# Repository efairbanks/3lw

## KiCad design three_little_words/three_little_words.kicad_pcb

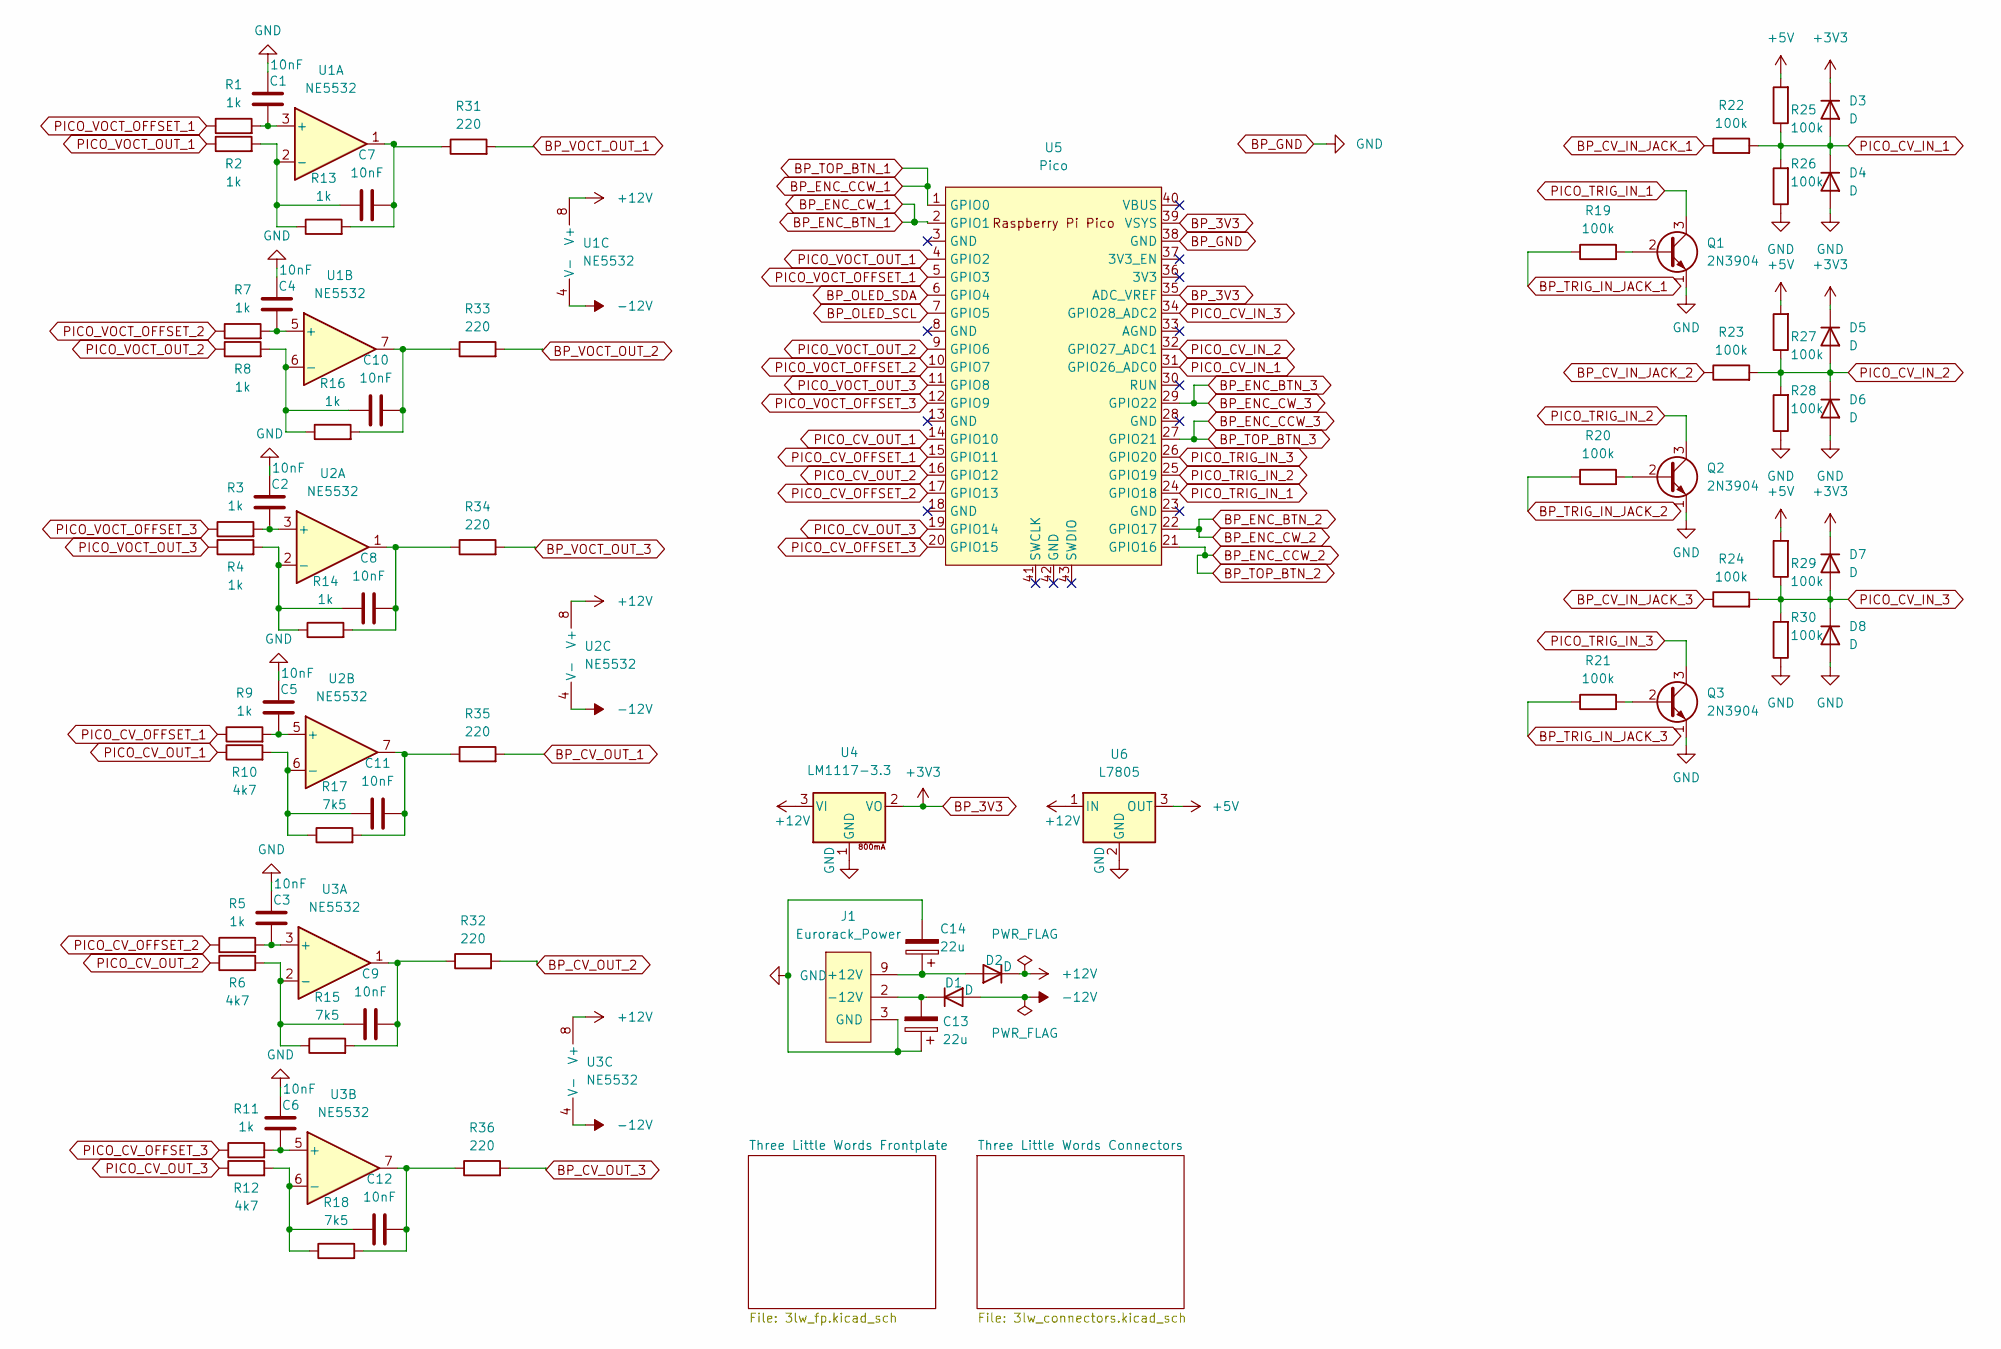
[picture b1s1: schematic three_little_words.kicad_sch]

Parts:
C1, C2, C3, C4, C5, C6, C7, C8, C9, C10, C11, C12: 10nF; C_Disc_D8.0mm_W2.5mm_P5.00mm
C13, C14: 22u; CP_Radial_D5.0mm_P2.50mm
D1, D2: D; D_DO-41_SOD81_P7.62mm_Horizontal
D3, D4, D5, D6, D7, D8: D; D_DO-35_SOD27_P7.62mm_Horizontal
J1: Eurorack_Power; mpn 302-S101
Q1, Q2, Q3: 2N3904; TO-92_Inline
R1, R2, R3, R4, R5, R7, R8, R9, R11, R13, R14, R16: 1k; R_Axial_DIN0207_L6.3mm_D2.5mm_P7.62mm_Horizontal
R6, R10, R12: 4k7; R_Axial_DIN0207_L6.3mm_D2.5mm_P7.62mm_Horizontal
R15, R17, R18: 7k5; R_Axial_DIN0207_L6.3mm_D2.5mm_P7.62mm_Horizontal
R19, R20, R21, R22, R23, R24, R25, R26, R27, R28, R29, R30: 100k; R_Axial_DIN0207_L6.3mm_D2.5mm_P7.62mm_Horizontal
R31, R32, R33, R34, R35, R36: 220; R_Axial_DIN0207_L6.3mm_D2.5mm_P7.62mm_Horizontal
U1, U2, U3: NE5532; DIP-8_W7.62mm
U4: LM1117-3.3; TO-220-3_Vertical; mpn LM1117IMP-3.3
U5: Pico; RPi_Pico_SMD_TH
U6: L7805; TO-220-3_Vertical

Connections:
+5V: R25.2, R27.2, R29.2, U6.3 (OUT)
+12V: D2.1 (K), U1.8 (V+), U2.8 (V+), U3.8 (V+), U4.3 (VI), U6.1 (IN)
-12V: D1.2 (A), U1.4 (V-), U2.4 (V-), U3.4 (V-)
BP_3V3: D3.1 (K), D5.1 (K), D7.1 (K), U4.2 (VO), U5.35 (ADC_VREF), U5.39 (VSYS); also elsewhere on the board
BP_CV_IN_JACK_1: R22.1; also elsewhere on the board
BP_CV_IN_JACK_2: R23.1; also elsewhere on the board
BP_CV_IN_JACK_3: R24.1; also elsewhere on the board
BP_CV_OUT_1: R35.2; also elsewhere on the board
BP_CV_OUT_2: R32.2; also elsewhere on the board
BP_CV_OUT_3: R36.2; also elsewhere on the board
BP_ENC_BTN_1: U5.2 (GPIO1); also elsewhere on the board
BP_ENC_BTN_2: U5.22 (GPIO17); also elsewhere on the board
BP_ENC_BTN_3: U5.29 (GPIO22); also elsewhere on the board
BP_ENC_CCW_1: U5.1 (GPIO0); also elsewhere on the board
BP_ENC_CCW_2: U5.21 (GPIO16); also elsewhere on the board
BP_ENC_CCW_3: U5.27 (GPIO21); also elsewhere on the board
BP_GND: C1.1, C2.1, C3.1, C4.1, C5.1, C6.1, C13.1, C14.2, D4.2 (A), D6.2 (A), D8.2 (A), J1.3 (GND), J1.4 (GND), J1.5 (GND), J1.6 (GND), J1.7 (GND), J1.8 (GND), Q1.1 (E), Q2.1 (E), Q3.1 (E), R26.1, R28.1, R30.1, U4.1 (GND), U5.38 (GND), U6.2 (GND); also elsewhere on the board
BP_OLED_SCL: U5.7 (GPIO5); also elsewhere on the board
BP_OLED_SDA: U5.6 (GPIO4); also elsewhere on the board
BP_TRIG_IN_JACK_1: R19.1; also elsewhere on the board
BP_TRIG_IN_JACK_2: R20.1; also elsewhere on the board
BP_TRIG_IN_JACK_3: R21.1; also elsewhere on the board
BP_VOCT_OUT_1: R31.2; also elsewhere on the board
BP_VOCT_OUT_2: R33.2; also elsewhere on the board
BP_VOCT_OUT_3: R34.2; also elsewhere on the board
unnamed: C1.2, R1.2, U1.3 (+)
unnamed: C2.2, R3.2, U2.3 (+)
unnamed: C3.2, R5.2, U3.3 (+)
unnamed: C4.2, R7.2, U1.5 (+)
unnamed: C5.2, R9.2, U2.5 (+)
unnamed: C6.2, R11.2, U3.5 (+)
unnamed: C7.1, R2.2, R13.1, U1.2 (-)
unnamed: C7.2, R13.2, R31.1, U1.1
unnamed: C8.1, R4.2, R14.1, U2.2 (-)
unnamed: C8.2, R14.2, R34.1, U2.1
unnamed: C9.1, R6.2, R15.1, U3.2 (-)
unnamed: C9.2, R15.2, R32.1, U3.1
unnamed: C10.1, R8.2, R16.1, U1.6 (-)
unnamed: C10.2, R16.2, R33.1, U1.7
unnamed: C11.1, R10.2, R17.1, U2.6 (-)
unnamed: C11.2, R17.2, R35.1, U2.7
unnamed: C12.1, R12.2, R18.1, U3.6 (-)
unnamed: C12.2, R18.2, R36.1, U3.7
unnamed: C13.2, D1.1 (K), J1.1 (-12V), J1.2 (-12V)
unnamed: C14.1, D2.2 (A), J1.9 (+12V), J1.10 (+12V)
unnamed: Q1.2 (B), R19.2
unnamed: Q2.2 (B), R20.2
unnamed: Q3.2 (B), R21.2
PICO_CV_IN_1: D3.2 (A), D4.1 (K), R22.2, R25.1, R26.2, U5.31 (GPIO26_ADC0)
PICO_CV_IN_2: D5.2 (A), D6.1 (K), R23.2, R27.1, R28.2, U5.32 (GPIO27_ADC1)
PICO_CV_IN_3: D7.2 (A), D8.1 (K), R24.2, R29.1, R30.2, U5.34 (GPIO28_ADC2)
PICO_CV_OFFSET_1: R9.1, U5.15 (GPIO11)
PICO_CV_OFFSET_2: R5.1, U5.17 (GPIO13)
PICO_CV_OFFSET_3: R11.1, U5.20 (GPIO15)
PICO_CV_OUT_1: R10.1, U5.14 (GPIO10)
PICO_CV_OUT_2: R6.1, U5.16 (GPIO12)
PICO_CV_OUT_3: R12.1, U5.19 (GPIO14)
PICO_TRIG_IN_1: Q1.3 (C), U5.24 (GPIO18)
PICO_TRIG_IN_2: Q2.3 (C), U5.25 (GPIO19)
PICO_TRIG_IN_3: Q3.3 (C), U5.26 (GPIO20)
PICO_VOCT_OFFSET_1: R1.1, U5.5 (GPIO3)
PICO_VOCT_OFFSET_2: R7.1, U5.10 (GPIO7)
PICO_VOCT_OFFSET_3: R3.1, U5.12 (GPIO9)
PICO_VOCT_OUT_1: R2.1, U5.4 (GPIO2)
PICO_VOCT_OUT_2: R8.1, U5.9 (GPIO6)
PICO_VOCT_OUT_3: R4.1, U5.11 (GPIO8)

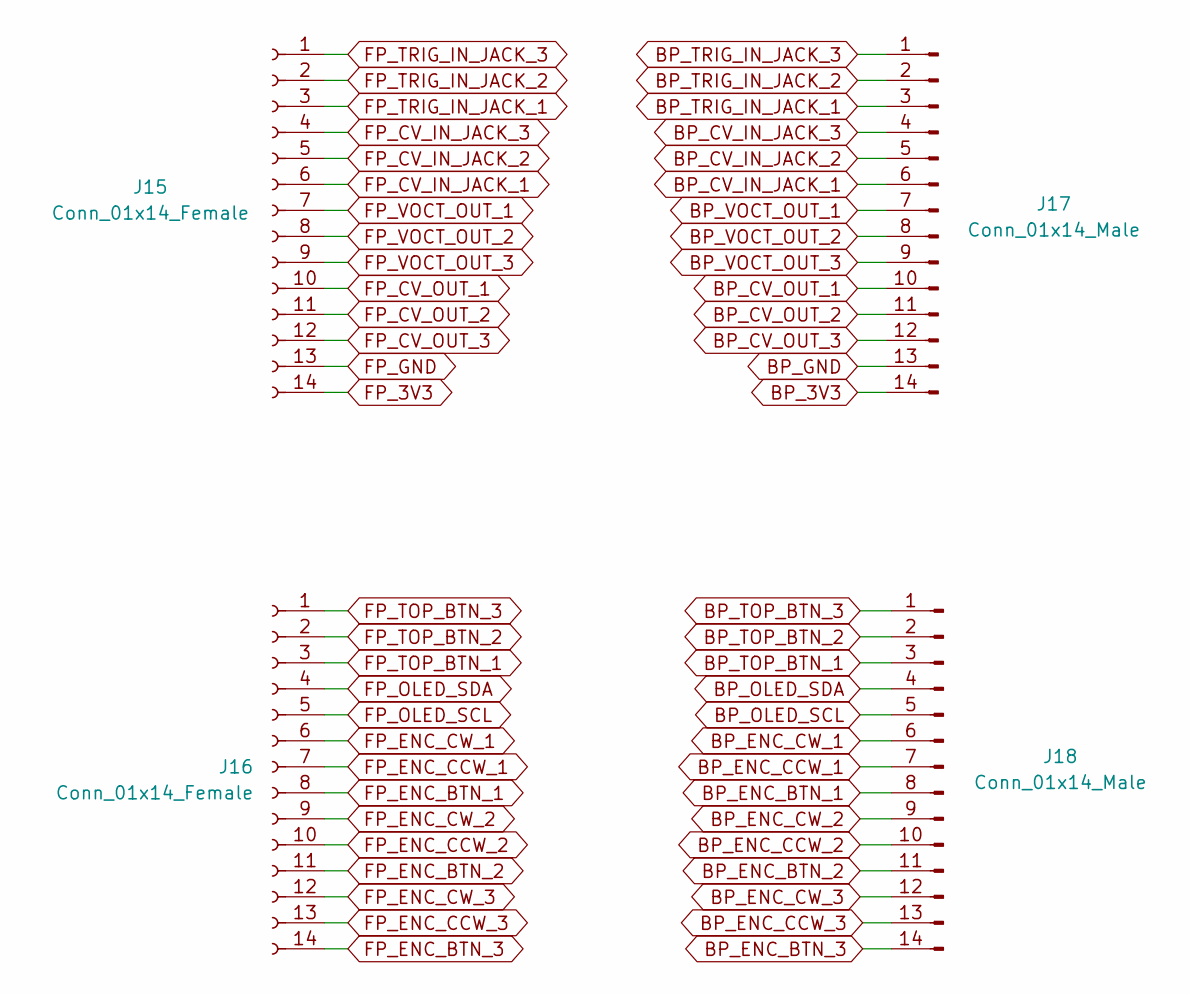
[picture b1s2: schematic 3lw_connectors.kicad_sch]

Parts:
J15, J16: Conn_01x14_Female; PinSocket_1x14_P2.54mm_Vertical
J17, J18: Conn_01x14_Male; PinHeader_1x14_P2.54mm_Vertical

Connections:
BP_3V3: J17.14; also elsewhere on the board
BP_CV_IN_JACK_1: J17.6; also elsewhere on the board
BP_CV_IN_JACK_2: J17.5; also elsewhere on the board
BP_CV_IN_JACK_3: J17.4; also elsewhere on the board
BP_CV_OUT_1: J17.10; also elsewhere on the board
BP_CV_OUT_2: J17.11; also elsewhere on the board
BP_CV_OUT_3: J17.12; also elsewhere on the board
BP_ENC_BTN_1: J18.6, J18.8; also elsewhere on the board
BP_ENC_BTN_2: J18.9, J18.11; also elsewhere on the board
BP_ENC_BTN_3: J18.12, J18.14; also elsewhere on the board
BP_ENC_CCW_1: J18.3, J18.7; also elsewhere on the board
BP_ENC_CCW_2: J18.2, J18.10; also elsewhere on the board
BP_ENC_CCW_3: J18.1, J18.13; also elsewhere on the board
BP_GND: J17.13; also elsewhere on the board
BP_OLED_SCL: J18.5; also elsewhere on the board
BP_OLED_SDA: J18.4; also elsewhere on the board
BP_TRIG_IN_JACK_1: J17.3; also elsewhere on the board
BP_TRIG_IN_JACK_2: J17.2; also elsewhere on the board
BP_TRIG_IN_JACK_3: J17.1; also elsewhere on the board
BP_VOCT_OUT_1: J17.7; also elsewhere on the board
BP_VOCT_OUT_2: J17.8; also elsewhere on the board
BP_VOCT_OUT_3: J17.9; also elsewhere on the board
FP_3V3: J15.14; also elsewhere on the board
FP_CV_IN_JACK_1: J15.6; also elsewhere on the board
FP_CV_IN_JACK_2: J15.5; also elsewhere on the board
FP_CV_IN_JACK_3: J15.4; also elsewhere on the board
FP_CV_OUT_1: J15.10; also elsewhere on the board
FP_CV_OUT_2: J15.11; also elsewhere on the board
FP_CV_OUT_3: J15.12; also elsewhere on the board
FP_ENC_BTN_1: J16.8; also elsewhere on the board
FP_ENC_BTN_2: J16.11; also elsewhere on the board
FP_ENC_BTN_3: J16.14; also elsewhere on the board
FP_ENC_CCW_1: J16.7; also elsewhere on the board
FP_ENC_CCW_2: J16.10; also elsewhere on the board
FP_ENC_CCW_3: J16.13; also elsewhere on the board
FP_ENC_CW_1: J16.6; also elsewhere on the board
FP_ENC_CW_2: J16.9; also elsewhere on the board
FP_ENC_CW_3: J16.12; also elsewhere on the board
FP_OLED_SCL: J16.5; also elsewhere on the board
FP_OLED_SDA: J16.4; also elsewhere on the board
FP_TOP_BTN_1: J16.3; also elsewhere on the board
FP_TOP_BTN_2: J16.2; also elsewhere on the board
FP_TOP_BTN_3: J16.1; also elsewhere on the board
FP_TRIG_IN_JACK_1: J15.3; also elsewhere on the board
FP_TRIG_IN_JACK_2: J15.2; also elsewhere on the board
FP_TRIG_IN_JACK_3: J15.1; also elsewhere on the board
FP_VOCT_OUT_1: J15.7; also elsewhere on the board
FP_VOCT_OUT_2: J15.8; also elsewhere on the board
FP_VOCT_OUT_3: J15.9; also elsewhere on the board

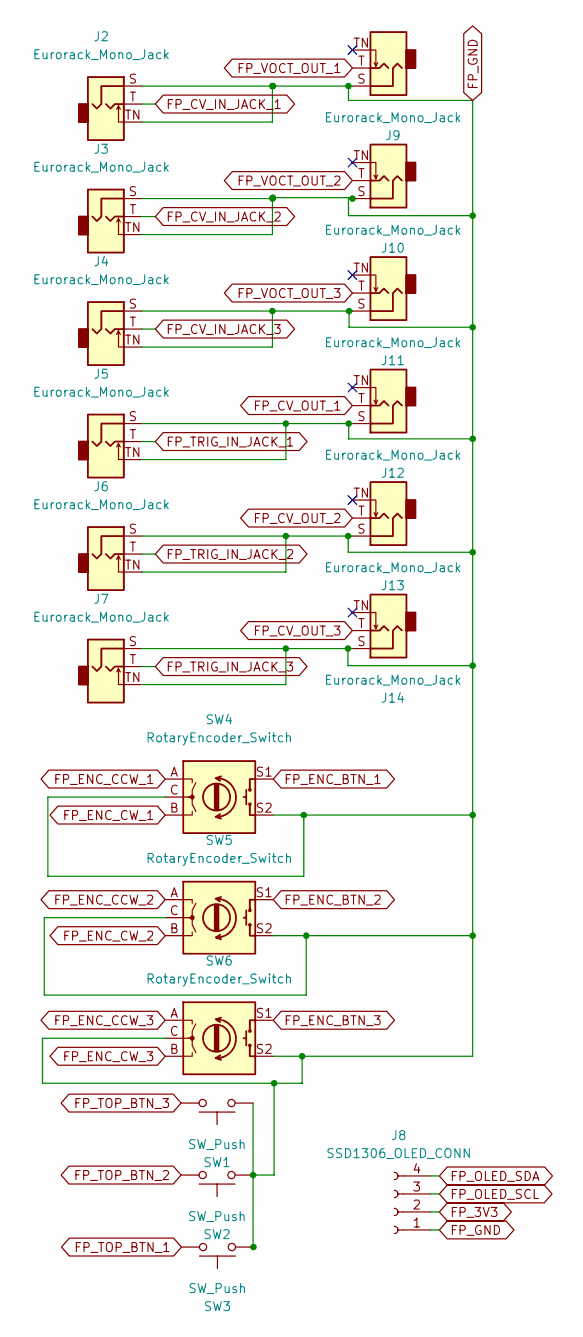
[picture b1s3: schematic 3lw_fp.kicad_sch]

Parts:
J2, J3, J4, J5, J6, J7, J9, J10, J11, J12, J13, J14: Eurorack_Mono_Jack; WQP518MA; mpn WQP-WQP518MA
J8: SSD1306_OLED_CONN; PinSocket_1x04_P2.54mm_Vertical
SW1, SW2, SW3: SW_Push; SW_PUSH_6mm
SW4, SW5, SW6: RotaryEncoder_Switch; RotaryEncoder_Alps_EC12E-Switch_Vertical_H20mm

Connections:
FP_3V3: J8.2; also elsewhere on the board
FP_CV_IN_JACK_1: J2.T (Tip); also elsewhere on the board
FP_CV_IN_JACK_2: J3.T (Tip); also elsewhere on the board
FP_CV_IN_JACK_3: J4.T (Tip); also elsewhere on the board
FP_CV_OUT_1: J12.T (Tip); also elsewhere on the board
FP_CV_OUT_2: J13.T (Tip); also elsewhere on the board
FP_CV_OUT_3: J14.T (Tip); also elsewhere on the board
FP_ENC_BTN_1: SW4.S1; also elsewhere on the board
FP_ENC_BTN_2: SW5.S1; also elsewhere on the board
FP_ENC_BTN_3: SW6.S1; also elsewhere on the board
FP_ENC_CCW_1: SW4.A; also elsewhere on the board
FP_ENC_CCW_2: SW5.A; also elsewhere on the board
FP_ENC_CCW_3: SW6.A; also elsewhere on the board
FP_ENC_CW_1: SW4.B; also elsewhere on the board
FP_ENC_CW_2: SW5.B; also elsewhere on the board
FP_ENC_CW_3: SW6.B; also elsewhere on the board
FP_OLED_SCL: J8.3; also elsewhere on the board
FP_OLED_SDA: J8.4; also elsewhere on the board
FP_TOP_BTN_1: SW3.2; also elsewhere on the board
FP_TOP_BTN_2: SW2.2; also elsewhere on the board
FP_TOP_BTN_3: SW1.2; also elsewhere on the board
FP_TRIG_IN_JACK_1: J5.T (Tip); also elsewhere on the board
FP_TRIG_IN_JACK_2: J6.T (Tip); also elsewhere on the board
FP_TRIG_IN_JACK_3: J7.T (Tip); also elsewhere on the board
FP_VOCT_OUT_1: J9.T (Tip); also elsewhere on the board
FP_VOCT_OUT_2: J10.T (Tip); also elsewhere on the board
FP_VOCT_OUT_3: J11.T (Tip); also elsewhere on the board

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
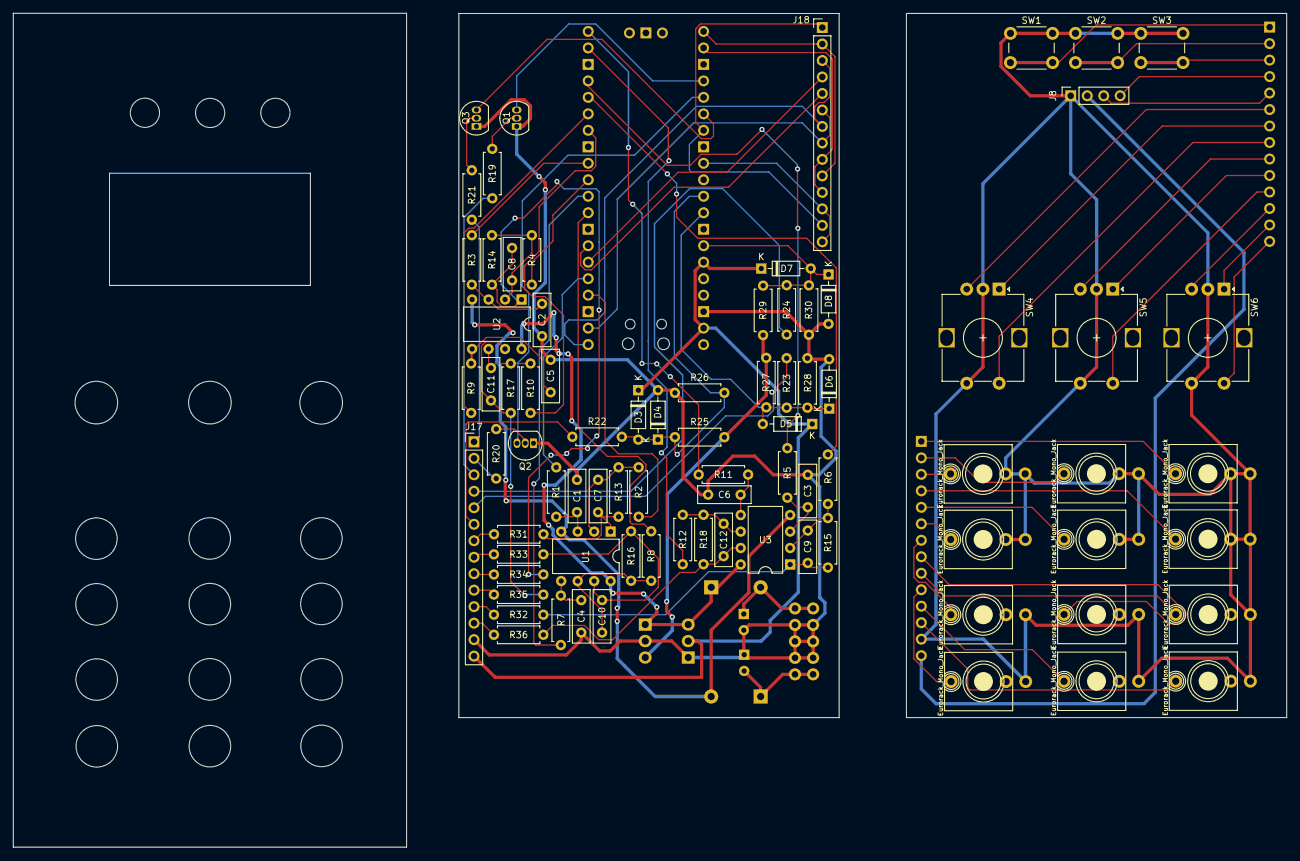
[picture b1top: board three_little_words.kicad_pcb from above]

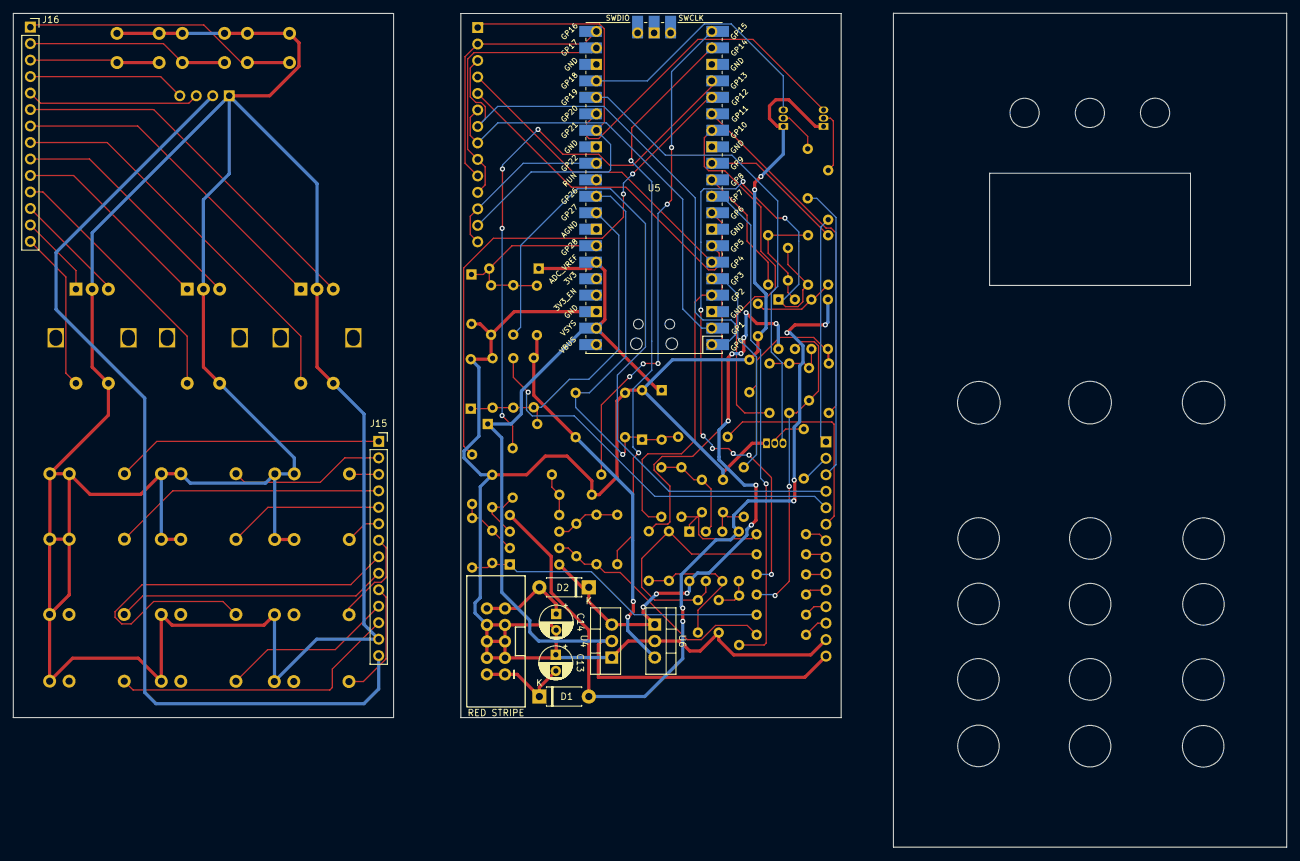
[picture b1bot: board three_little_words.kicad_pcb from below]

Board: 2 copper layers, 196.2 x 128.5 mm, 95 parts (10 on the bottom side), 94 nets.

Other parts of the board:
 : MountingHole_M3_Slotted_Eurorack
 #2,  #3,  #4: MountingHole_M3_Slotted_Eurorack

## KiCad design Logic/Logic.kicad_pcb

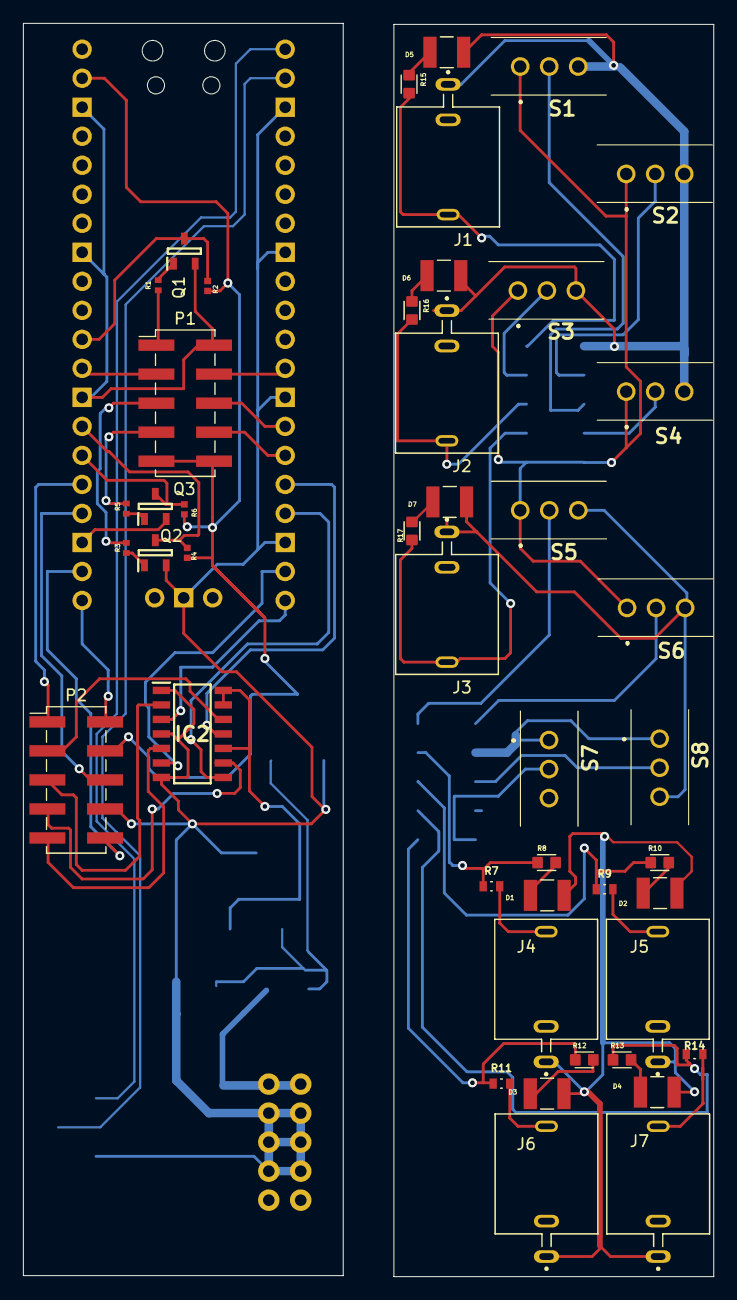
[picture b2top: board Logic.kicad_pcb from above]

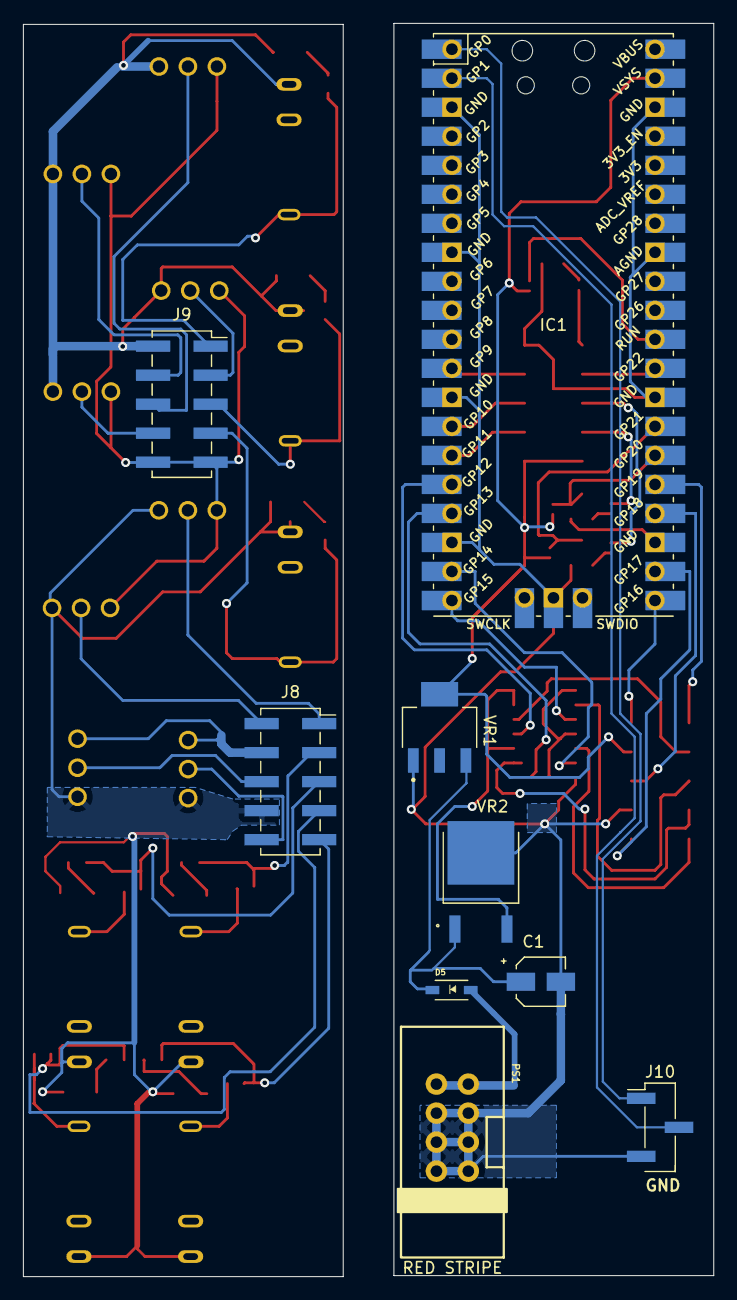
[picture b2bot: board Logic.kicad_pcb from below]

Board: 2 copper layers, 60.4 x 109.7 mm, 54 parts (9 on the bottom side), 26 nets.

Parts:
C1: CAP_EEE-FT1E220AR
D1, D2, D3, D4, D5, D6, D7: LED-APD3224SURCK-F01
D5#2: SOD3715X145N; Diode-1N5819HW-7-F
IC1: RPi_Pico_SMD_TH
IC2: SN74HCS125QBQARQ1
J1, J2, J3, J4, J5, J6, J7: PJ3410; THONK_PJ398SM-12
J8, J9: PinSocket_2x05_P2.54mm_Vertical_SMD
J10: PinHeader_1x03_P2.54mm_Vertical_SMD_Pin1Left
P1, P2: PinHeader_2x05_P2.54mm_Vertical_SMD
PS1: Eurorack_Power_2x5_Shrouded
Q1, Q2, Q3: MMBT3904215
R1, R3, R5: In Resist-ERJ-2RKF1003X
R2, R4, R6: RES10k_CRGCQ0402F10K
R7, R9, R11, R14: Out Resist-RES_ERJPA3D1001V
R8, R10, R12, R13, R15, R16, R17: RESC1608X50N
S1, S2, S3, S4, S5, S6, S7, S8: 200MSP3T1B1M2QEH
VR1: VREG_LM1117IMPX-3.3/NOPB; VREG_LM1117IMPX-3.3_NOPB
VR2: VREG_L7805CDT-TR

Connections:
3.3V: IC1.39, J8.4, J9.9, J9.10, P1.9, P1.10, P2.4, R2.2, R4.2, R6.2, S1.1, S2.1, S3.1, S4.1, S5.1, S6.1, S7.1, S8.1, VR1.2, VR1.4
5V: IC2.10, IC2.13, IC2.14, VR2.2
Bus-16: IC2.12, J4.3, J8.3, P2.3, R7.1, R7.2, R8.1
Bus-17: IC2.9, J7.3, J8.7, P2.7, R13.1, R14.1, R14.2
Bus-19: IC2.5, J6.3, J8.9, P2.9, R11.1, R11.2, R12.1
Bus-20: IC2.2, J5.3, J8.5, P2.5, R9.1, R9.2, R10.1
Ground: C1.2, D1.2, D2.2, D3.2, D4.2, D5.2, D6.2, D7.2, IC1.3, IC1.8, IC1.13, IC1.18, IC1.23, IC1.28, IC1.33, IC1.38, IC1.42, IC2.1, IC2.4, IC2.7, J1.1, J2.1, J3.1, J4.1, J5.1, J6.1, J7.1, J8.8, J9.2, J10.3, P1.2, P2.8, PS1.3, PS1.4, PS1.5, PS1.6, PS1.7, PS1.8, Q1.2, Q2.2, Q3.2, S1.3, S2.3, S3.3, S4.3, S5.3, S6.3, S7.3, S8.3, VR1.1, VR2.3
Pico: Q1.1, Q2.1, Q3.1, R1.2, R3.2, R5.2
Pico-12: IC1.12, J9.4, P1.4, S2.2
Pico-14: IC1.14, J9.6, P1.6, S1.2
Pico-15: IC1.15, J9.8, P1.8, S4.2
Pico-16: IC1.16, IC2.11
Pico-17: IC1.17, IC2.8
Pico-19: IC1.19, IC2.6
Pico-20: IC1.20, IC2.3
Pico-21: IC1.21, J8.2, P2.2, S6.2
Pico-22: IC1.22, J8.10, P2.10, S7.2
Pico-24: IC1.24, J8.6, P2.6, S8.2
Pico-25: IC1.25, J8.1, P2.1, S5.2
Pico-26: IC1.26, J3.3, J9.7, P1.7, Q3.3, R5.1, R6.1, R17.1
Pico-27: IC1.27, J2.3, J9.5, P1.5, Q2.3, R3.1, R4.1, R16.2
Pico-29: IC1.29, J9.3, P1.3, S3.2
Pico-30: IC1.30, J1.3, J9.1, P1.1, Q1.3, R1.1, R2.1, R15.2
Power: C1.1, D5#2.A, D5#2.C, PS1.9, PS1.10, VR1.3, VR2.1
i2c-SCL: IC1.2, J10.2
i2c-SDA: IC1.1, J10.1

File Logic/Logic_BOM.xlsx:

Item # | Designator | Quantity | Manufacturer | Mfg Part # | Descripton / Value | Package / Footprint | Type | Notes
1 | J10 | 1 | (i2c pins) |  | PinHeader_1x03_P2.54mm_Vertical_SMD_Pin1Left | SMT 3P | SMD
2 | R10,R12,R8,R13,R15,R16,R17 | 7 | TE Connectivity | CRG0603F300R | 300 Ohms ±1% 0.1W, 1/10W Chip Resistor 0603 (1608 Metric) Thick Film, 1622912-1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 | 1608 | SMD
3 | R11,R14,R7,R9 | 4 | Panasonic | ERJ-PA3D1001V | Thick Film Resistors - SMD 0603 1Kohm 0.5% Anti-Surge AEC-Q200 | 1608 | SMD
4 | S6,S8,S5,S1,S7,S3,S2,S4 | 8 | E-Switch | 200MSP3T1B1M2QEH | SWITCH TOGGLE SPDT 3A 120V | SPDT | DNS | Do not include in assembly
5 | Q3,Q2,Q1 | 3 | Nexperia | MMBT3904215 | Bipolar Transistors - BJT TRANS SW TAPE-7 MMBT3904/SOT23/TO-236AB | SOT-23-3 | SMD
6 | D4,D2,D1,D3,D5,D6,D7 | 7 | Kingbright | APD3224SURCK-F01 | Standard LEDs - SMD Red Water Clear 635nm 1000mcd | 3224 | SMD
7 | J3,J1,J6,J4,J7,J5,J2 | 7 | Thonk | PJ398SM-12 | Thonkiconn Mono 3.5mm Audio Jacks | 3POS | DNS | Do not include in assembly
8 | R2,R6,R4 | 3 | TE Connectivity | CRGCQ0402F10K | Fixed Resistor CRGCQ 0402 10K 1% | 1005 | SMD
9 | P1,P2 | 2 | (connector pins) |  | PinHeader_2x05_P2.54mm_Vertical_SMD | SMT 10P | SMD
10 | R5,R1,R3 | 3 | Panasonic | ERJ-2RKF1003X | 100 kOhms ±1% 0.1W, 1/10W Chip Resistor 0402 (1005 Metric) Automotive AEC-Q200 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 | 1005 | SMD
11 | IC2 | 1 | Texas Instruments | SN74HCS125QBQARQ1 | Automotive Schmitt-trigger inputs quadruple bus buffer gates with 3-state outpu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 | SOIC-14 | SMD
12 | VR1 | 1 | Texas Instruments | LM1117IMPX-3.3/NOPB | LDO Voltage Regulators 800MA LDO LINEAR REG | SOT-223-4 | SMD
13 | VR2 | 1 | STMicroelectronics | L7805CDT-TR | Linear Voltage Regulators 5.0V 1.0A Positive | DPAK | SMD
14 | IC1 | 1 | Raspberry Pi | Raspberry Pi Pico | Through hole straight pin header, 2x20, 2.54mm pitch, double rows | 40POS | DNS | Do not include in assembly
15 | D5 | 1 | Diodes Incorporated | 1N5819HW-7-F | Schottky Diodes & Rectifiers Vr/40V Io/1A T/R | SOD-123-2 | SMD
16 | PS1 | 1 |  |  | Eurorack_Power_2x5_Shrouded | 10POS | DNS | Do not include in assembly
17 | C1 | 1 | Panasonic | EEE-FT1E220AR | Aluminum Electrolytic Capacitors - SMD 22uF 25volts 4x5.8mm SMD | SMT 2P | SMD
18 | J9,J8 | 2 | (connector sockets) |  | PinSocket_2x05_P2.54mm_Vertical_SMD |  | SMD

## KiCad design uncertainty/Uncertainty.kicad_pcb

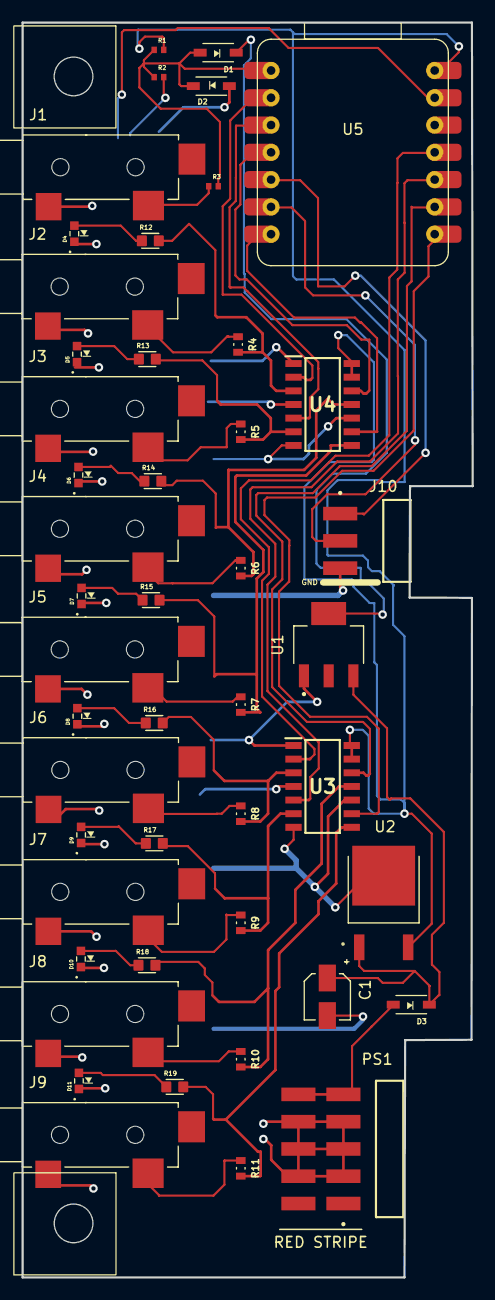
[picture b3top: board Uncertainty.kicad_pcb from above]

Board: 2 copper layers, 41.9 x 116.8 mm, 49 parts (0 on the bottom side), 15 nets.

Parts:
C1: CAP_EEE-FT1E220AR
D1, D2, D3: SOD3715X145N; Diode-1N5819HW-7-F
D4, D5, D6, D7, D8, D9, D10, D11: LED_APGA1602SEC-E-KA
H1, H2: Keystone 633
J1, J2, J3, J4, J5, J6, J7, J8, J9: SWITCHCRAFT_35RASMT2AHNTRX
J10: SAMTEC_TSM-103-01-L-SH
PS1: SAMTEC_TSM-105-01-L-DH
R1, R2, R3: In Resist-ERJ-2RKF1003X
R4, R5, R6, R7, R8, R9, R10, R11: Out Resist-RES_ERJPA3D1001V
R12, R13, R14, R15, R16, R17, R18, R19: RESC1608X50N
U1: VREG_LM1117IMPX-3.3/NOPB; VREG_LM1117IMPX-3.3_NOPB
U2: VREG_L7805CDT-TR
U3, U4: SN74HCS125QBQARQ1
U5: XIAO-RP2040

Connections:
3.3V: D1.C, U1.4
5V: R1.2, U2.2, U3.13, U3.14, U4.13, U4.14, U5.14
Ground: C1.2, D2.A, D4.C, D5.C, D6.C, D7.C, D8.C, D9.C, D10.C, D11.C, J1.5, J2.5, J3.5, J4.5, J5.5, J6.5, J7.5, J8.5, J9.5, J10.03, PS1.03, PS1.04, PS1.05, PS1.06, PS1.07, PS1.08, R2.2, U1.1, U2.3, U3.1, U3.4, U3.7, U3.10, U4.1, U4.4, U4.7, U4.10, U5.13
Power: C1.1, D3.A, D3.C, PS1.09, PS1.10, U1.2, U1.3, U2.1
Signal-In: D1.A, D2.C, J1.4, R1.1, R2.1, R3.1, R3.2, U5.1
Signal-Out1: D4.A, J2.4, R4.1, R4.2, R12.1, R12.2, U4.2, U4.3, U5.2
Signal-Out2: D5.A, J3.4, R5.1, R5.2, R13.1, R13.2, U4.5, U4.6, U5.3
Signal-Out3: D6.A, J4.4, R6.1, R6.2, R14.1, R14.2, U4.11, U4.12, U5.4
Signal-Out4: D7.A, J5.4, R7.1, R7.2, R15.1, R15.2, U4.8, U4.9, U5.7
Signal-Out5: D8.A, J6.4, R8.1, R8.2, R16.1, R16.2, U3.2, U3.3, U5.11
Signal-Out6: D9.A, J7.4, R9.1, R9.2, R17.1, R17.2, U3.5, U3.6, U5.10
Signal-Out7: D10.A, J8.4, R10.1, R10.2, R18.1, R18.2, U3.11, U3.12, U5.9
Signal-Out8: D11.A, J9.4, R11.1, R11.2, R19.2, U3.8, U3.9, U5.8
i2c-SCL: J10.02, U5.6
i2c-SDA: J10.01, U5.5

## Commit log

2022-03-22 Initial commit.
2022-04-19 I love you. <3
2022-04-19 Adding code for Three Little Words.
2022-04-19 Fixing some issues /w setting defines that were causing a bad math to happen.
2022-04-19 Fixing bug because we were printing an uninit'd buffer. Oops!
2022-04-19 Updating gitignore, adding support for multiple "apps" running concurrently, or selecting apps.
2022-04-20 Adding 220ohm resistors to outputs
2022-04-20 Adding footprints for various components of 3lw.
2022-04-21 Adding BOM, footprints, starting circuit.
2022-04-21 Adding circuitsss.
2022-04-22 Tried to sort circuit. Mixed success.
2022-05-01 Finishing 3lw schematic
2022-05-02 Adding gerbers for first run of three little words.
2022-05-16 Reorganizing code.
2022-05-16 Merge.
2022-05-18 Lots of changes to hardware interface. Top button and encoder values are mirrored from one another, so that's not ideal!
2022-05-20 More changes to hardware, adding gate ins, testing v/oct out.
2022-05-21 Various.
2022-06-01 Massive update.
2022-06-17 Regular update.
2022-07-02 Added Uncertainty KiCad files
2022-07-02 Footprints used for Uncertainty
2022-07-25 Latest updates
2022-07-25 Uncertainty BOM
2022-07-25 Add new directory
2022-07-25 Initial upload-Kate's Logic files
2022-07-28 pinout fixes, better nets
2022-07-28 Quad bus part update
2022-07-28 Input LEDs and other tweaks
2022-07-28 Input LEDs and resistors added
2022-07-31 more fixes!
2022-08-02 LED and cap/diode fixes
2022-08-02 bus pins grounded and other little fixes
2022-09-22 Soooo many changes.
2022-09-23 Uncertainty - updated dimensions and sample faceplate
2022-09-24 New LEDs added
2022-09-24 updated footprint library
2022-09-24 New LEDs and mounting hardware
2023-02-14 Adding most recent changes to 3LW apps pending code cleanup and restructure.
2023-02-16 Deep restructure and rewrite of parts of 3LW. Trying to make the code more readable, use fixed-point math more judiciously, remove dead code, etc... Also want to rework input and output hardware inte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
2023-02-22 Adding three track sequencer.
2023-03-04 Lots of magic so that analog ins track pretty accurately. Huge rework of env gen.
2023-08-06 Adding new chordgen big word.
